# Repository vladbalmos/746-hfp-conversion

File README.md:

## British GPO 746 bluetooth conversion (HFP)

Firmware and hardware related resources for adding hands-free bluetooth support to a 746 british phone.

## Hardware requirements

* esp32 devboard (v1)
* Raspberry PI Pico
* external DAC (TLC5615)
* GPO 746 telephone

## Software dependencies

* esp-idf (v5.1)
* pico-sdk ( >= v1.5.0)
* opencd (optional)
* picoprobe (optiona)

## Audio input/output

In a nutshell, the ESP32 is configured with `SCO data path = HCI`, this enables the improved mSBC codec on some AGs; the audio in/out is received/sent from/to a Raspberry Pi Pico I2C slave, acting as a recording/playback device.  
The microphone is sampled using the Pico's 12bit ADC, while the earpiece speaker is driven by a buffered 10bit external DAC which interfaces with the Pico using SPI.

This is more complicated than it should mostly due to my lack of experience with the ESP32 and lack of a propper external ADC.  
My initial plan was to use the ESP32's ADC & DAC simultaneous, but the I've run into the following problems:
1. the ADC & DAC cannot be used at the same time in DMA Mode, since they both share the same DMA fifo of the I2S0 peripheral: [ADC continuous mode Hardware Limitations](https://docs.espressif.com/projects/esp-idf/en/v5.1/esp32/api-reference/peripherals/adc_continuous.html?highlight=adc_continuous_read#hardware-limitations) - I couldn't find any proper way of making it work
2. even if both ADC & DAC could work in continuous DMA mode, the ADC configuration doesn't allow sampling frequencies below 20khz (for mSBC & CVSD codecs a lower sampling rate is required: 16khz, 8khz respectively)
3. the ESP32 doesn't have an analog ground which makes both the ADC & DAC really noisy

In a previous iteration of the project, both the Pico and the external DAC were connected to the ESP32 via SPI, but it struggled to keep a constant rate of sending/receiving PCM samples during an active call because each PCM sample required its own SPI transaction (both the Pico and the TLC5615 support only 2 byte transactions) - this caused horrible audio on both ends.

## Audio transmission
The Pico is configured as a slave I2C device receiving and transmitting audio data at the master's request (ESP32). Data is transmitted via a basic protocol built on top of I2C which consists of 5 commands. Each command is encoded as a 16 bit uint. The first 8 MSB encode the command code and the last 8 LSB encode any arguments the command might have.  
Commands:  

* AUDIO_ENABLE  
    Enable ADC/DAC. The sample rate is given as a parameter
* AUDIO_DISABLE  
    Disable ADC/DAC
* AUDIO_POLL
    Poll the slave for new audio data sampled by the ADC. If slave returns `true`, the AUDIO_RECEIVE command is sent to the slave to receive the PCM samples
* AUDIO_TRANSMIT
    Sent by the master to transmit PCM samples for playback
* AUDIO_RECEIVE
    Sent by the master to receive new PCM samples from the ADC

Basic data flow between ESP32 and PICO:

    1. (master) send AUDIO_ENABLE command
       (slave) initialize ADC & DAC using the sample rate encoded in the command
       (slave) respond with OK
    2. (master) transmit any buffered PCM samples for playback (AUDIO_TRANSMIT)
       (slave) receive PCM samples and transmit to DAC via DMA
    3. (master) poll slave for new samples (AUDIO_POLL). If reply is OK, send AUDIO_RECEIVE command to receive new samples

## Functions

Almost all the existing features of the GPO 746 are preserved once paired via Bluetooth HFP:

* Ringing works when an incoming call is detected. The ringer is driven by a AC coupled PWM 20hz signal amplified to 34V using a DC-DC voltage booster module.
* Earpiece / microphone
* Dialing via the rotary dialer works as expected

Visual indicator LEDs available for:

* power
* ringing
* bluetooth connection state
* handset on/off hook

A schematic on how to physically connect the phone to the board will be added soon.

## Building

The boards need to be separately flashed using the code in `src`.

### esp32

    cd src/esp32
    source /path/to/esp-idf/export.sh
    idf.py build flash

### pico
If using picoprobe and opencd:

    # open pico-install.sh.template and change the path to opencd binary
    # rename pico-install.sh.template to pico-install.sh
    # make pico-install.sh executable
    # copy pico-install.sh to a folder which is in your $PATH (I usually place this little scripts in ~/bin)
    cd src/pico
    make install

If not using picoprobe & opencd just build and flash using the manual steps provided in the getting started pico-sdk guide

## PCBs
The device is split into two PCBs, a main board and a control board. The main board houses all the relevant components for bluetooth and audio while the control board contains the indicator LEDs and a microswitch for toggling bluetooth pairing. The schematics and PCB designs were done using KiCad, all documents are inside the `hw` folder. I designed the main board to be single sided, but the pcb design file contains traces and vias for a two sided board only to pass DRC validation and given that I manually trace and etch my PCBs I cannot guarantee that the final designs are good enough for sending to a PCB manufacturer. Inspect the designs and tweak accordingly before ordering a set of boards. You can find some pictures of the boards in the `img` folder. 

A 3d printed case model will be available in the future inside `hw/3d-prints`.

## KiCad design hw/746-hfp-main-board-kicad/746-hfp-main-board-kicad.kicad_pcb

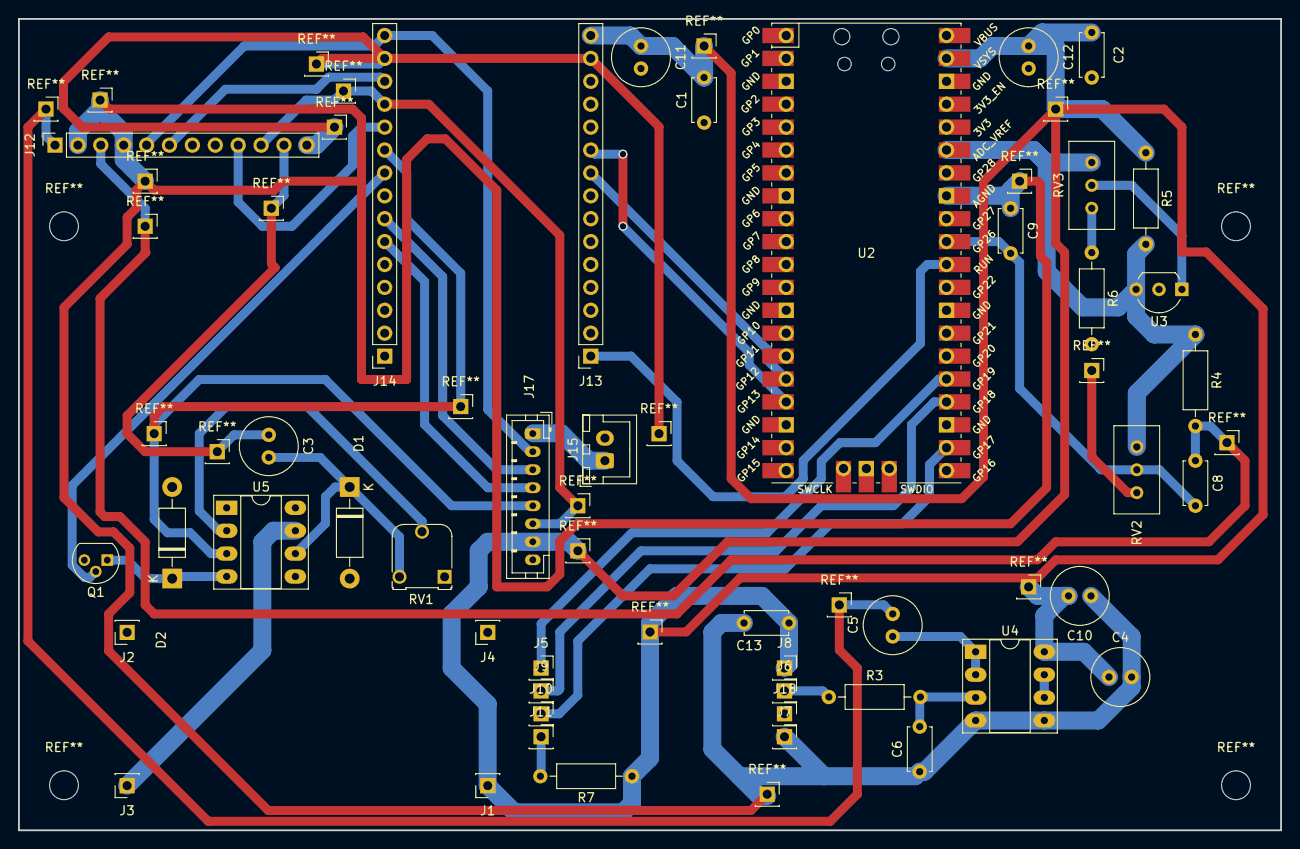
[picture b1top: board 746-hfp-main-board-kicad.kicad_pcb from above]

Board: 2 copper layers, 140.0 x 90.0 mm, 44 parts (0 on the bottom side), 33 nets.

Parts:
C1, C2, C13: 0.1uf; C_Disc_D4.7mm_W2.5mm_P5.00mm
C3: 47uF; C_Radial_D6.3mm_H11.0mm_P2.50mm
C4, C5, C11, C12: 220uF; C_Radial_D6.3mm_H11.0mm_P2.50mm
C6: 3.3nF; C_Disc_D4.7mm_W2.5mm_P5.00mm
C8: 10uF; C_Disc_D4.7mm_W2.5mm_P5.00mm
C9: 0.1uF; C_Disc_D4.7mm_W2.5mm_P5.00mm
C10: 0.1uF; C_Radial_D6.3mm_H11.0mm_P2.50mm
D1, D2: 1N5819; D_DO-41_SOD81_P10.16mm_Horizontal
J1: 5V; PinSocket_1x01_P2.54mm_Vertical
J2, J4: GND; PinSocket_1x01_P2.54mm_Vertical
J3: 34V; PinSocket_1x01_P2.54mm_Vertical
J5, J6, J7, J8, J9, J10, J11, J18: Conn_01x01_Socket; PinSocket_1x01_P2.54mm_Vertical
J12: Phone_Connector; PinSocket_1x12_P2.54mm_Vertical
J13: ESP32_Left_Pins; PinSocket_1x15_P2.54mm_Vertical
J14: ESP32_Right_Pins; PinSocket_1x15_P2.54mm_Vertical
J15: Power_Connector; JST_XH_B2B-XH-A_1x02_P2.50mm_Vertical
J17: Control_board_connector; JST_PH_B8B-PH-K_1x08_P2.00mm_Vertical
Q1: IRFZ44N; TO-92
R3, R7: 10k; R_Axial_DIN0207_L6.3mm_D2.5mm_P10.16mm_Horizontal
R4: 1k; R_Axial_DIN0207_L6.3mm_D2.5mm_P10.16mm_Horizontal
R5: 330; R_Axial_DIN0207_L6.3mm_D2.5mm_P10.16mm_Horizontal
R6: 100k; R_Axial_DIN0207_L6.3mm_D2.5mm_P10.16mm_Horizontal
RV1: 100k; Potentiometer_Runtron_RM-065_Vertical
RV2: 10k; Potentiometer_Bourns_3296W_Vertical
RV3: 100k; Potentiometer_Bourns_3296W_Vertical
U2: Pico; RPi_Pico_SMD_TH
U3: TL431P; TO-92_Inline_Wide
U4: LM358; DIP-8_W7.62mm_Socket_LongPads
U5: UA741; DIP-8_W7.62mm_Socket_LongPads

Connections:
+3.3V: J12.5, J14.15, J17.2
+3.3V_Clean: R4.1, R5.2, RV2.3, RV3.1, U2.35 (ADC_VREF), U3.1 (K)
+5V: C1.2, C2.2, C4.1, C10.2, C11.1, C12.1, C13.1, J1.1, J8.1, J13.15, J17.7, R5.1, R7.1, U2.39 (VSYS), U4.8 (V+)
+5V_pre_switch: J15.1, J17.1
+34V: J3.1, U5.7 (V+)
Audio_SCL (27): J13.10, U2.17 (GPIO13)
Audio_SDA (26): J13.9, U2.16 (GPIO12)
BT_LED_STATE (19): J14.6, J17.4
DAC_CS (17): J10.1, U2.22 (GPIO17)
DAC_SCLK (18): J9.1, U2.24 (GPIO18)
DAC_TX_Din (19): J5.1, U2.25 (GPIO19)
DAC_Vout: J6.1, R3.1
DOut: J11.1, R7.2
Dialer (15): J12.6, J14.13
ENABLE_PAIRING_BTN (18): J14.7, J17.3
GND: C1.1, C2.1, C11.2, C12.2, D1.2 (A), D2.2 (A), J2.1, J4.1, J12.7, J12.8, J12.12, J13.14, J14.14, J15.2, J17.8, Q1.3 (S), R6.2, RV1.1, RV2.1, U2.3 (GND), U2.8 (GND), U2.13 (GND), U2.18 (GND), U2.23 (GND), U2.28 (GND), U2.38 (GND)
GNDA: C4.2, C6.1, C9.1, C10.1, C13.2, J7.1, J12.2, J12.4, U2.33 (AGND), U4.4 (V-), U4.5 (+)
HookSwitchOut (2): J12.10, J14.12, J17.6
HookSwitchPower (4): J12.9, J14.11
Mic+: C8.1, J12.3, R4.2
Mosfet_Drain: D2.1 (K), Q1.1 (D), U5.4 (V-)
unnamed: C3.2, D1.1 (K), RV1.3, U5.6
unnamed: R6.1, RV3.3
unnamed: C8.2, C9.2, RV2.2, U2.31 (GPIO26_ADC0)
unnamed: C6.2, R3.2, U4.3 (+)
unnamed: C5.1, U4.1, U4.2 (-)
unnamed: U4.6 (-), U4.7
unnamed: RV1.2, U5.2 (-)
Pico_Enable: J13.1, U2.30 (RUN)
Ringer+: C3.1, J12.11
RingerEnabled (17): J14.9, Q1.2 (G)
RingerSignal (16): J14.10, J17.5, U5.3 (+)
Speaker+: C5.2, J12.1

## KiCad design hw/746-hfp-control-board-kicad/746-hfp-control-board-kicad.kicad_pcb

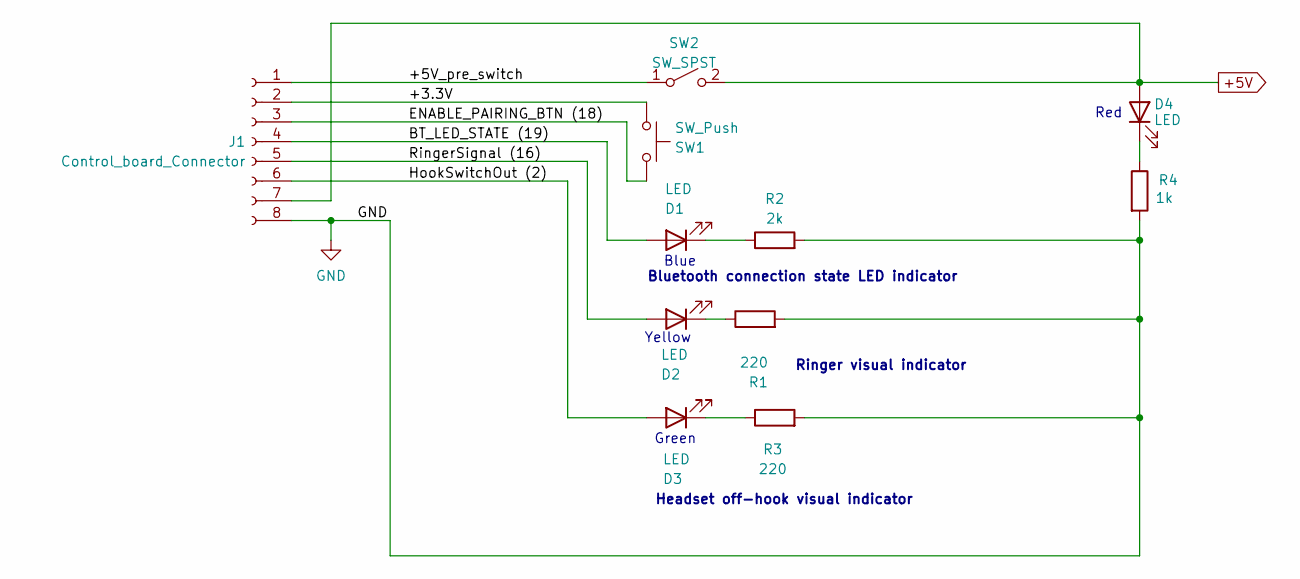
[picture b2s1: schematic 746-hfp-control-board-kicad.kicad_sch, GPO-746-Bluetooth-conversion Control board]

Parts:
D1, D2, D3, D4: LED; LED_D5.0mm
J1: Control_board_Connector; PinSocket_1x08_P2.54mm_Vertical
R1, R3: 220; R_Axial_DIN0207_L6.3mm_D2.5mm_P10.16mm_Horizontal
R2: 2k; R_Axial_DIN0207_L6.3mm_D2.5mm_P10.16mm_Horizontal
R4: 1k; R_Axial_DIN0207_L6.3mm_D2.5mm_P10.16mm_Horizontal
SW1: SW_Push; SW_PUSH_6mm_H5mm
SW2: SW_SPST; PinHeader_1x02_P2.54mm_Vertical

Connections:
+5V: D4.2 (A), J1.7, SW2.2 (B)
/+3.3V: J1.2, SW1.1
/+5V_pre_switch: J1.1, SW2.1 (A)
/BT_LED_STATE (19): D1.2 (A), J1.4
/ENABLE_PAIRING_BTN (18): J1.3, SW1.2
/HookSwitchOut (2): D3.2 (A), J1.6
/RingerSignal (16): D2.2 (A), J1.5
GND: J1.8, R1.2, R2.2, R3.2, R4.2
unnamed: D1.1 (K), R2.1
unnamed: D2.1 (K), R1.1
unnamed: D3.1 (K), R3.1
unnamed: D4.1 (K), R4.1

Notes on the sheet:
Headset off-hook visual indicator
Yellow
Blue
Bluetooth connection state LED indicator
Red
Green
Ringer visual indicator

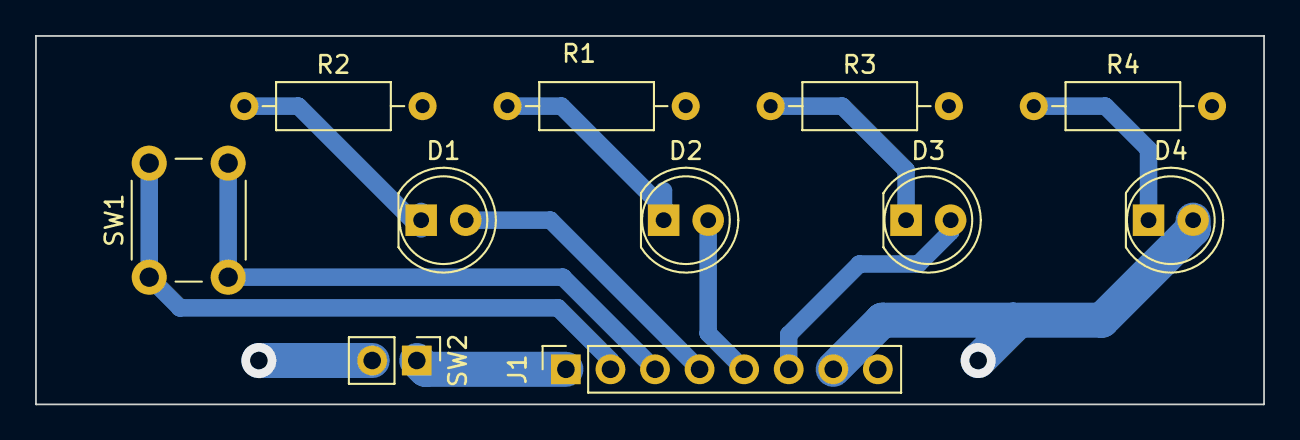
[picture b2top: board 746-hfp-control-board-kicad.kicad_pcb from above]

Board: 2 copper layers, 70.0 x 21.0 mm, 11 parts (0 on the bottom side), 12 nets.

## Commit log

2023-06-11 Proof of concept: Capturing ADC through DMA and writing to SPI DAC
2023-06-18 Generate correct 10bit@44.1khz sine wave
2023-06-18 Refactoring
2023-06-24 Fix DMA timing issue
2023-06-25 Bug fixes
2023-06-25 Cleanup
2023-06-25 Improvements
2023-06-25 WIPP
2023-06-26 Bugs
2023-06-28 Fixed issue with DAC
2023-06-28 Bug fix
2023-07-13 Add ringer support
2023-07-16 Start working on dialer
2023-07-17 Finish dialer implementation
2023-07-23 Remove bluetooth related code
2023-07-25 Start clean with esp32
2023-07-27 Fix hook switch debouncing
2023-07-28 Update configuration
2023-07-28 Replaced printf with ESP_LOG statements
2023-07-31 Finally a working receive audio example
2023-08-01 Add basic ringing, call answering & hangup support
2023-08-09 Work in progress
2023-08-10 Init/deinit bug fixes
2023-08-10 Increase debug interval
2023-08-10 Toggle discoverability once paired
2023-08-10 Start work on audio capture
2023-08-17 Change pins and esp_timer to gptimer
2023-08-17 Add schematic
2023-08-19 Working SPI DAC
2023-08-19 Working on CVSD, not on mSBC
2023-08-20 Start integrating Pico's ADC
2023-08-20 Move code to dedicated src folder
2023-08-21 Proof of concept ADC via SPI
2023-08-22 Set correct adc dma timer
2023-08-23 WIP - Almost working
2023-08-26 Switch to i2c adc
2023-08-26 Stuff
2023-08-27 Mostly working
2023-08-27 Improve documentation
2023-08-28 Stable(ish)
2023-08-31 Enable test mode
2023-09-02 Disable logging statistics
2023-09-02 Optimize for performance
2023-09-02 Update schematic
2023-09-03 Bug fixes. Add volume change support
2023-09-03 Cleanup & improvements
2023-09-03 Add bluetooth state led and pairing controls
2023-09-04 Improve schematic
2023-09-05 Improved schematic
2023-09-05 Generate bill of materials
2023-09-07 Change scl pin
2023-09-07 Create pcb board
2023-09-07 Rename kicad main board
2023-09-07 Add schematic & pcb for control board
2023-09-08 Create kicad pcb
2023-09-11 Improve kicad related
2023-09-18 Fixed pcb
2023-09-20 Fixed board
2023-09-20 Added BOM
2023-09-20 Add images
2023-10-07 Start work on enclosure
2023-10-07 Update sketch
